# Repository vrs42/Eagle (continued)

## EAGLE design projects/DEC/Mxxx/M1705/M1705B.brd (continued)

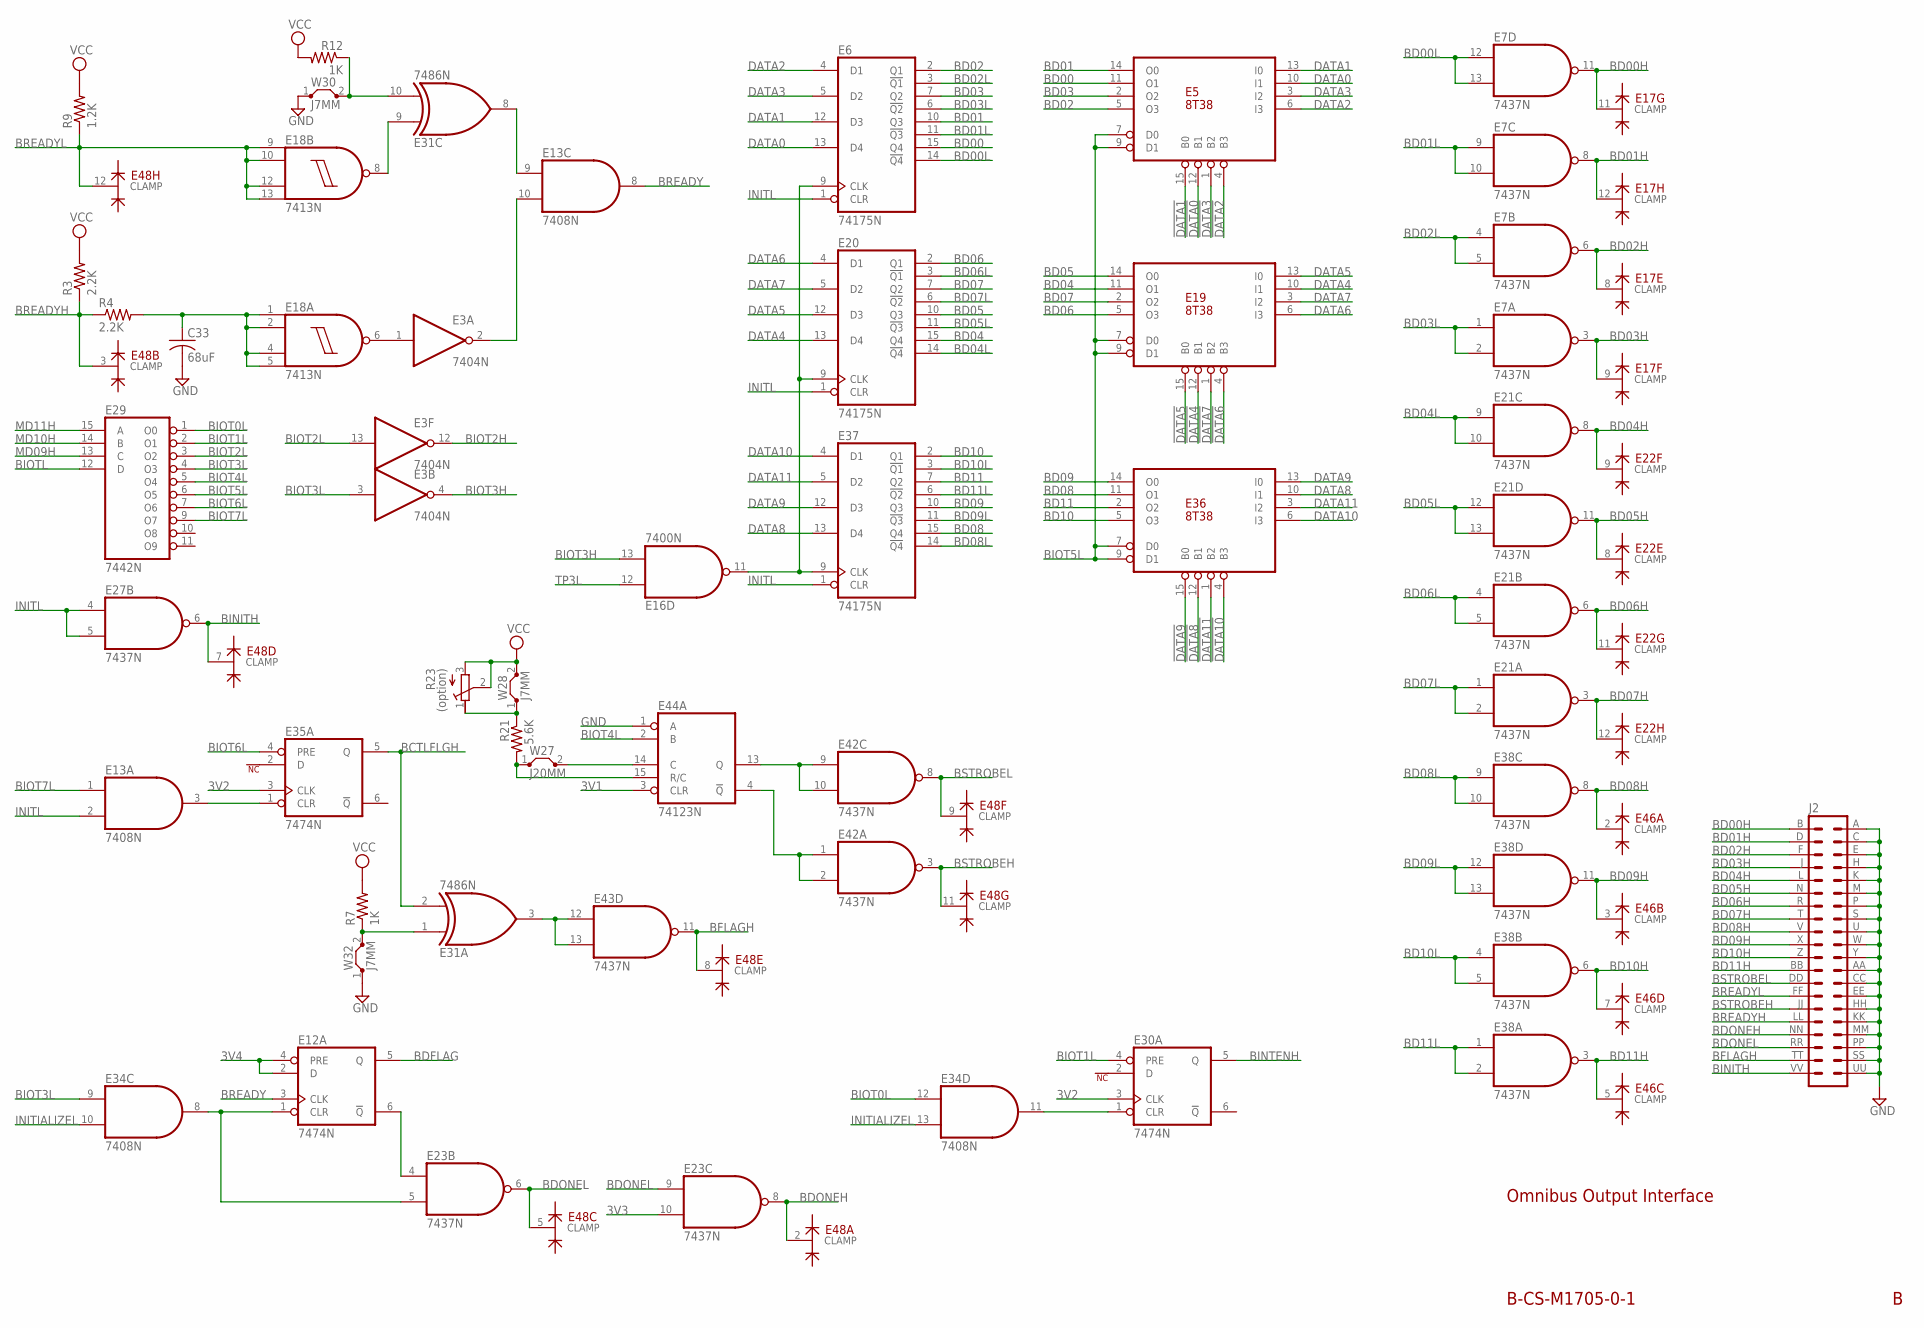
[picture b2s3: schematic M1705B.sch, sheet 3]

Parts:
C33: 68uF; C102-043X133
E3: 7404N; DIL14
E5, E19, E36: 8T38; DIL16
E6, E20, E37: 74175N; DIL16
E7, E21, E23, E27, E38, E42, E43: 7437N; DIL14
E12, E30, E35: 7474N; DIL14
E13, E34: 7408N; DIL14
E16: 7400N; DIL14
E17, E22, E46, E48: DEC2501; DIL14
E18: 7413N; DIL14
E29: 7442N; DIL16
E31: 7486N; DIL14
E44: 74123N; DIL16
J2: DEC40PINH
R3, R4: 2.2K; 0207/10
R7, R12: 1K; 0207/10
R9: 1.2K; 0207/10
R21: 5.6K; 0207/10
R23: (option); 3006Y
W27: J20MM; 20
W28, W30, W32: J7MM; 07

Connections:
3V1: E44.3 (CLR); also elsewhere on the board
3V2: E30.3 (CLK), E35.3 (CLK); also elsewhere on the board
3V3: E23.10 (I1); also elsewhere on the board
3V4: E12.2 (D), E12.4 (PRE); also elsewhere on the board
!DATA0: E5.12 (B1); also elsewhere on the board
!DATA1: E5.15 (B0); also elsewhere on the board
!DATA2: E5.4 (B3); also elsewhere on the board
!DATA3: E5.1 (B2); also elsewhere on the board
!DATA4: E19.12 (B1); also elsewhere on the board
!DATA5: E19.15 (B0); also elsewhere on the board
!DATA6: E19.4 (B3); also elsewhere on the board
!DATA7: E19.1 (B2); also elsewhere on the board
!DATA8: E36.12 (B1); also elsewhere on the board
!DATA9: E36.15 (B0); also elsewhere on the board
!DATA10: E36.4 (B3); also elsewhere on the board
!DATA11: E36.1 (B2); also elsewhere on the board
BCTLFLGH: E31.2 (I1), E35.5 (Q)
BD00: E5.11 (O1), E6.15 (Q4)
BD00H: E7.11 (O), E17.11 (CLAMP), J2.B (2)
BD00L: E6.14 (!Q4), E7.12 (I0), E7.13 (I1)
BD01: E5.14 (O0), E6.10 (Q3)
BD01H: E7.8 (O), E17.12 (CLAMP), J2.D (4)
BD01L: E6.11 (!Q3), E7.9 (I0), E7.10 (I1)
BD02: E5.5 (O3), E6.2 (Q1)
BD02H: E7.6 (O), E17.8 (CLAMP), J2.F (6)
BD02L: E6.3 (!Q1), E7.4 (I0), E7.5 (I1)
BD03: E5.2 (O2), E6.7 (Q2)
BD03H: E7.3 (O), E17.9 (CLAMP), J2.J (8)
BD03L: E6.6 (!Q2), E7.1 (I0), E7.2 (I1)
BD04: E19.11 (O1), E20.15 (Q4)
BD04H: E21.8 (O), E22.9 (CLAMP), J2.L (10)
BD04L: E20.14 (!Q4), E21.9 (I0), E21.10 (I1)
BD05: E19.14 (O0), E20.10 (Q3)
BD05H: E21.11 (O), E22.8 (CLAMP), J2.N (12)
BD05L: E20.11 (!Q3), E21.12 (I0), E21.13 (I1)
BD06: E19.5 (O3), E20.2 (Q1)
BD06H: E21.6 (O), E22.11 (CLAMP), J2.R (14)
BD06L: E20.3 (!Q1), E21.4 (I0), E21.5 (I1)
BD07: E19.2 (O2), E20.7 (Q2)
BD07H: E21.3 (O), E22.12 (CLAMP), J2.T (16)
BD07L: E20.6 (!Q2), E21.1 (I0), E21.2 (I1)
BD08: E36.11 (O1), E37.15 (Q4)
BD08H: E38.8 (O), E46.2 (CLAMP), J2.V (18)
BD08L: E37.14 (!Q4), E38.9 (I0), E38.10 (I1)
BD09: E36.14 (O0), E37.10 (Q3)
BD09H: E38.11 (O), E46.3 (CLAMP), J2.X (20)
BD09L: E37.11 (!Q3), E38.12 (I0), E38.13 (I1)
BD10: E36.5 (O3), E37.2 (Q1)
BD10H: E38.6 (O), E46.7 (CLAMP), J2.Z (22)
BD10L: E37.3 (!Q1), E38.4 (I0), E38.5 (I1)
BD11: E36.2 (O2), E37.7 (Q2)
BD11H: E38.3 (O), E46.5 (CLAMP), J2.BB (24)
BD11L: E37.6 (!Q2), E38.1 (I0), E38.2 (I1)
BDFLAG: E12.5 (Q); also elsewhere on the board
BDONEH: E23.8 (O), E48.2 (CLAMP), J2.NN (34)
BDONEL: E23.6 (O), E23.9 (I0), E48.5 (CLAMP), J2.RR (36)
BFLAGH: E43.11 (O), E48.8 (CLAMP), J2.TT (38)
BINITH: E27.6 (O), E48.7 (CLAMP), J2.VV (40)
BINTENH: E30.5 (Q); also elsewhere on the board
BIOT0L: E29.1 (O0), E34.12 (I0)
BIOT1L: E29.2 (O1), E30.4 (PRE)
BIOT2H: E3.12 (O); also elsewhere on the board
BIOT2L: E3.13 (I), E29.3 (O2)
BIOT3H: E3.4 (O), E16.13 (I1)
BIOT3L: E3.3 (I), E29.4 (O3), E34.9 (I0)
BIOT4L: E29.5 (O4), E44.2 (B)
BIOT5L: E5.7 (D0), E5.9 (D1), E19.7 (D0), E19.9 (D1), E29.6 (O5), E36.7 (D0), E36.9 (D1); also elsewhere on the board
BIOT6L: E29.7 (O6), E35.4 (PRE)
BIOT7L: E13.1 (I0), E29.9 (O7)
BIOTL: E29.12 (D); also elsewhere on the board
BREADY: E12.3 (CLK), E13.8 (O)
BREADYH: E48.3 (CLAMP), J2.LL (32), R3.1, R4.1
BREADYL: E18.9 (I0), E18.10 (I1), E18.12 (I2), E18.13 (I3), E48.12 (CLAMP), J2.FF (28), R9.1
BSTROBEH: E42.3 (O), E48.11 (CLAMP), J2.JJ (30)
BSTROBEL: E42.8 (O), E48.9 (CLAMP), J2.DD (26)
DATA0: E5.10 (I1), E6.13 (D4); also elsewhere on the board
DATA1: E5.13 (I0), E6.12 (D3); also elsewhere on the board
DATA2: E5.6 (I3), E6.4 (D1); also elsewhere on the board
DATA3: E5.3 (I2), E6.5 (D2); also elsewhere on the board
DATA4: E19.10 (I1), E20.13 (D4); also elsewhere on the board
DATA5: E19.13 (I0), E20.12 (D3); also elsewhere on the board
DATA6: E19.6 (I3), E20.4 (D1); also elsewhere on the board
DATA7: E19.3 (I2), E20.5 (D2); also elsewhere on the board
DATA8: E36.10 (I1), E37.13 (D4); also elsewhere on the board
DATA9: E36.13 (I0), E37.12 (D3); also elsewhere on the board
DATA10: E36.6 (I3), E37.4 (D1); also elsewhere on the board
DATA11: E36.3 (I2), E37.5 (D2); also elsewhere on the board
GND: C33.2, E3.7 (GND), E5.8 (GND), E6.8 (GND), E7.7 (GND), E12.7 (GND), E13.7 (GND), E16.7 (GND), E17.14 (GND), E18.7 (GND), E19.8 (GND), E20.8 (GND), E21.7 (GND), E22.14 (GND), E23.7 (GND), E27.7 (GND), E29.8 (GND), E30.7 (GND), E31.7 (GND), E34.7 (GND), E35.7 (GND), E36.8 (GND), E37.8 (GND), E38.7 (GND), E42.7 (GND), E43.7 (GND), E44.1 (A), E44.8 (GND), E46.14 (GND), E48.14 (GND), J2.A (1), J2.AA (23), J2.C (3), J2.CC (25), J2.E (5), J2.EE (27), J2.H (7), J2.HH (29), J2.K (9), J2.KK (31), J2.M (11), J2.MM (33), J2.P (13), J2.PP (35), J2.S (15), J2.SS (37), J2.U (17), J2.UU (39), J2.W (19), J2.Y (21), W30.1, W32.1; also elsewhere on the board
INITIALIZEL: E34.10 (I1), E34.13 (I1); also elsewhere on the board
INITL: E6.1 (CLR), E13.2 (I1), E20.1 (CLR), E27.4 (I0), E27.5 (I1), E37.1 (CLR); also elsewhere on the board
MD09H: E29.13 (C); also elsewhere on the board
MD10H: E29.14 (B); also elsewhere on the board
MD11H: E29.15 (A); also elsewhere on the board
unnamed: E3.2 (O), E13.10 (I1)
unnamed: E3.1 (I), E18.6 (O)
unnamed: E6.9 (CLK), E16.11 (O), E20.9 (CLK), E37.9 (CLK)
unnamed: E12.1 (CLR), E23.5 (I1), E34.8 (O)
unnamed: E12.6 (!Q), E23.4 (I0)
unnamed: E31.10 (I1), R12.1, W30.2
unnamed: E31.1 (I0), R7.1, W32.2
unnamed: E13.3 (O), E35.1 (CLR)
unnamed: E13.9 (I0), E31.8 (O)
unnamed: C33.1, E18.1 (I0), E18.2 (I1), E18.4 (I2), E18.5 (I3), R4.2
unnamed: E18.8 (O), E31.9 (I0)
unnamed: E31.3 (O), E43.12 (I0), E43.13 (I1)
unnamed: E30.1 (CLR), E34.11 (O)
unnamed: E44.14 (C), W27.2
unnamed: R21.1, R23.1 (A), W28.1
unnamed: E42.1 (I0), E42.2 (I1), E44.4 (!Q)
unnamed: E42.9 (I0), E42.10 (I1), E44.13 (Q)
unnamed: E44.15 (R/C), R21.2, W27.1
TP3L: E16.12 (I0); also elsewhere on the board
VCC: E3.14 (VCC), E5.16 (VCC), E6.16 (VCC), E7.14 (VCC), E12.14 (VCC), E13.14 (VCC), E16.14 (VCC), E17.1 (VCC), E18.14 (VCC), E19.16 (VCC), E20.16 (VCC), E21.14 (VCC), E22.1 (VCC), E23.14 (VCC), E27.14 (VCC), E29.16 (VCC), E30.14 (VCC), E31.14 (VCC), E34.14 (VCC), E35.14 (VCC), E36.16 (VCC), E37.16 (VCC), E38.14 (VCC), E42.14 (VCC), E43.14 (VCC), E44.16 (VCC), E46.1 (VCC), E48.1 (VCC), R3.2, R7.2, R9.2, R12.2, R23.2 (S), R23.3 (E), W28.2; also elsewhere on the board

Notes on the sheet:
B-CS-M1705-0-1
Omnibus Output Interface

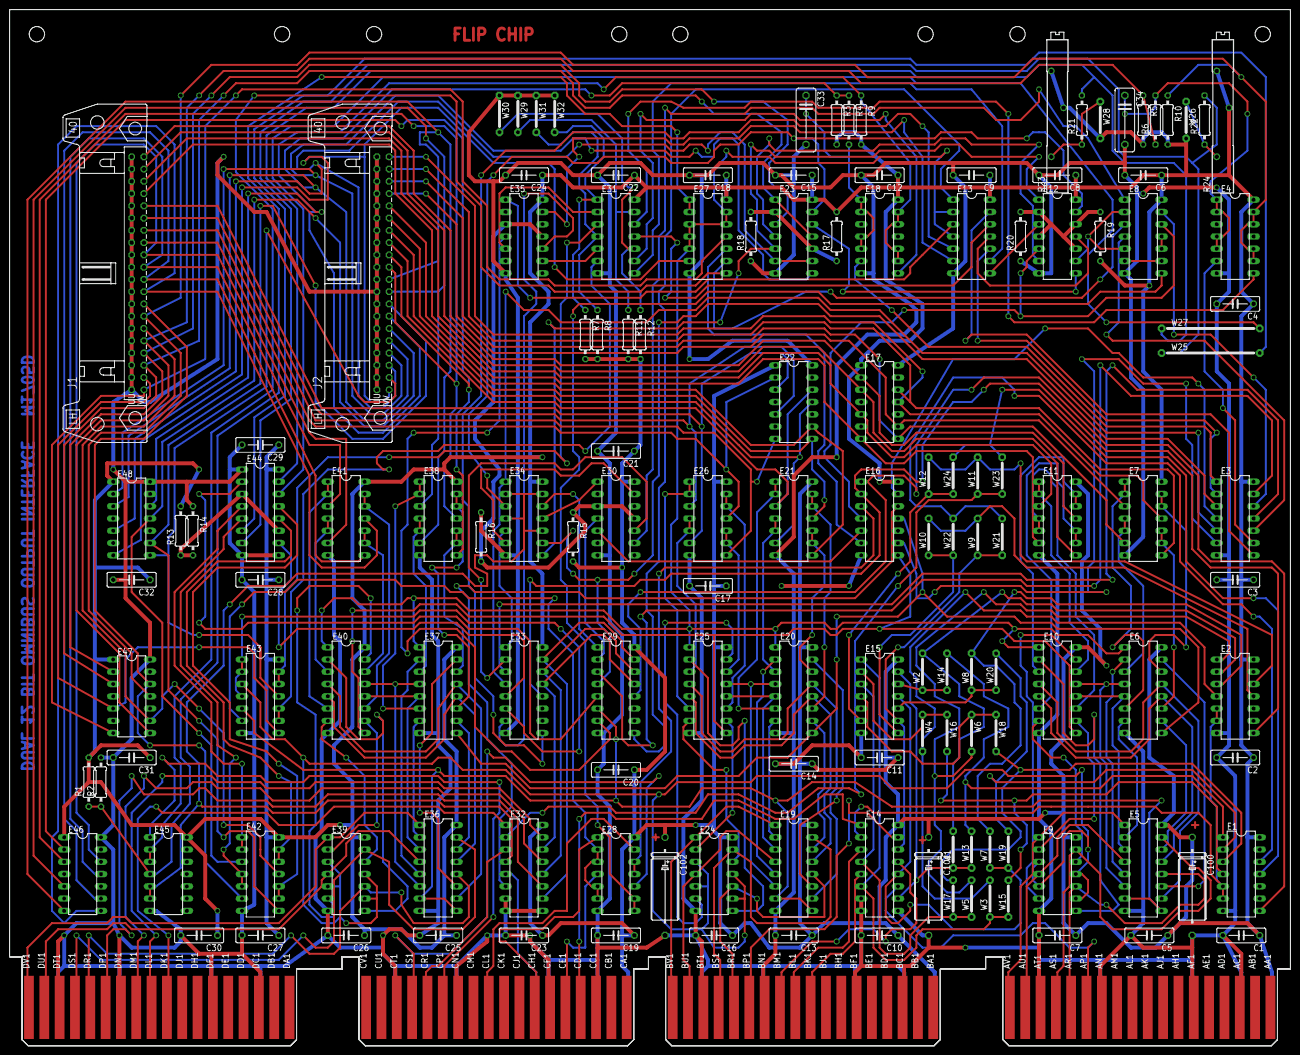
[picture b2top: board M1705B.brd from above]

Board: 3 copper layers, 265.3 x 214.6 mm, 146 parts (0 on the bottom side), 242 nets.

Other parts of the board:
U$3: FLIPCHIP

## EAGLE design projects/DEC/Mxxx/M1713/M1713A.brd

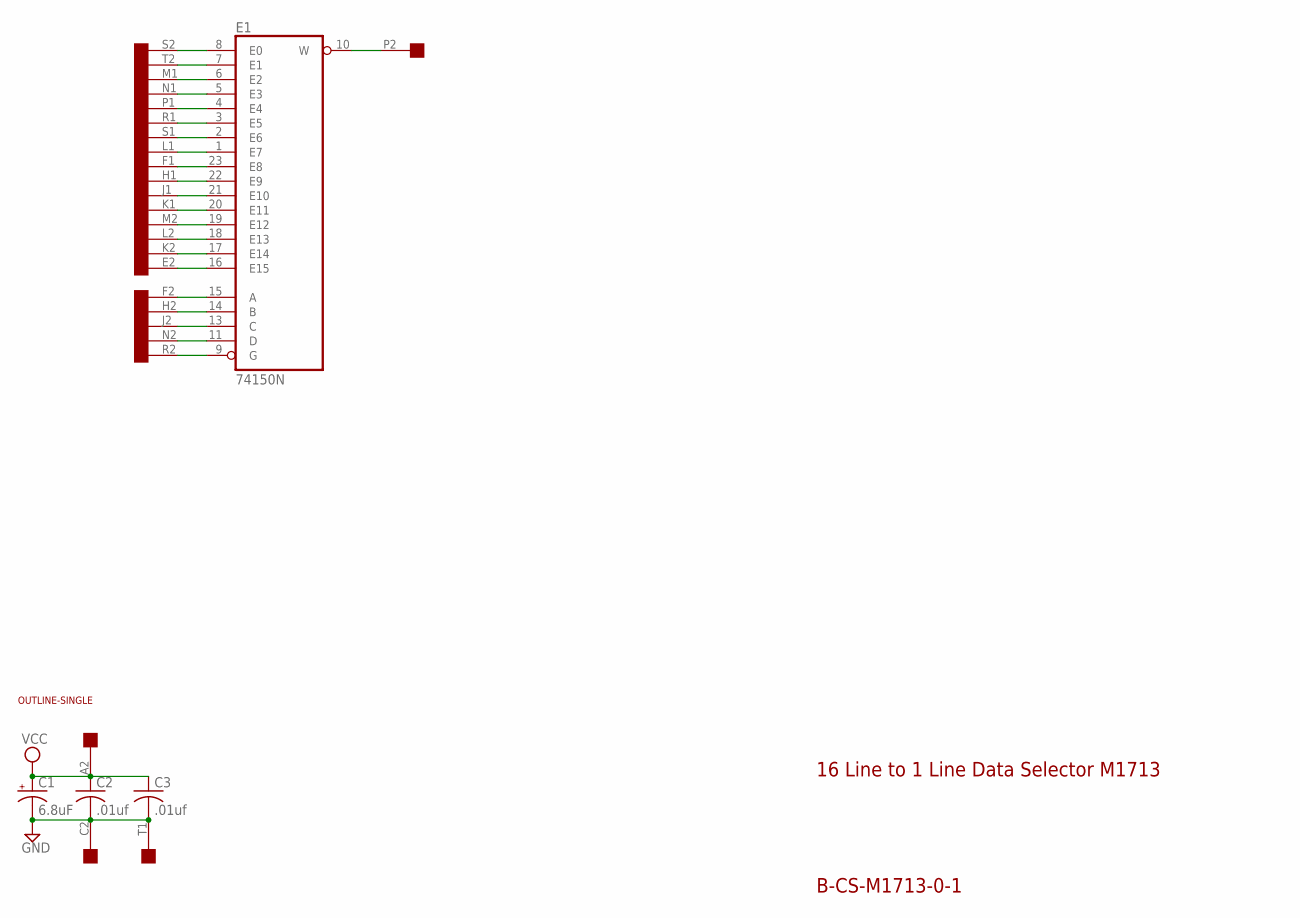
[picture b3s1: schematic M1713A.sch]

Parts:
C1: 6.8uF; E22-6
C2, C3: .01uf; C050-025X075
E1: 74150N; DIL24-6
U$1: OUTLINE-SINGLE; SINGLE
U$2: EDGE-2CONNECTOR; EDGE-CON2

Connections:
GND: C1.-, C2.2, C3.2, E1.12 (GND), U$2.C2, U$2.T1
unnamed: E1.8 (E0), U$2.S2
unnamed: E1.6 (E2), U$2.M1
unnamed: E1.5 (E3), U$2.N1
unnamed: E1.4 (E4), U$2.P1
unnamed: E1.3 (E5), U$2.R1
unnamed: E1.2 (E6), U$2.S1
unnamed: E1.10 (W), U$2.P2
unnamed: E1.23 (E8), U$2.F1
unnamed: E1.1 (E7), U$2.L1
unnamed: E1.22 (E9), U$2.H1
unnamed: E1.20 (E11), U$2.K1
unnamed: E1.21 (E10), U$2.J1
unnamed: E1.19 (E12), U$2.M2
unnamed: E1.7 (E1), U$2.T2
unnamed: E1.18 (E13), U$2.L2
unnamed: E1.17 (E14), U$2.K2
unnamed: E1.16 (E15), U$2.E2
unnamed: E1.15 (A), U$2.F2
unnamed: E1.14 (B), U$2.H2
unnamed: E1.13 (C), U$2.J2
unnamed: E1.11 (D), U$2.N2
unnamed: E1.9 (G), U$2.R2
VCC: C1.+, C2.1, C3.1, E1.24 (VCC), U$2.A2

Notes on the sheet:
B-CS-M1713-0-1
16 Line to 1 Line Data Selector M1713

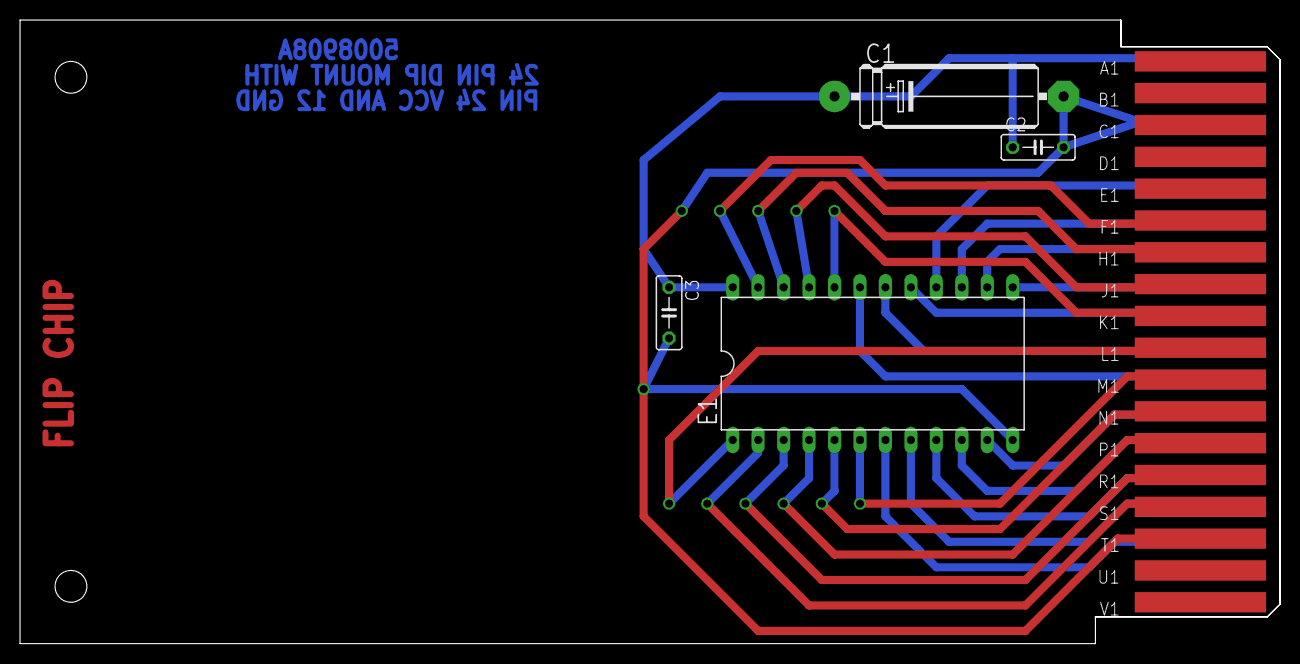
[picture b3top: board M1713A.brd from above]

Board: 2 copper layers, 125.7 x 62.2 mm, 7 parts (0 on the bottom side), 24 nets.

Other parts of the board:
U$3: FLIPCHIP
